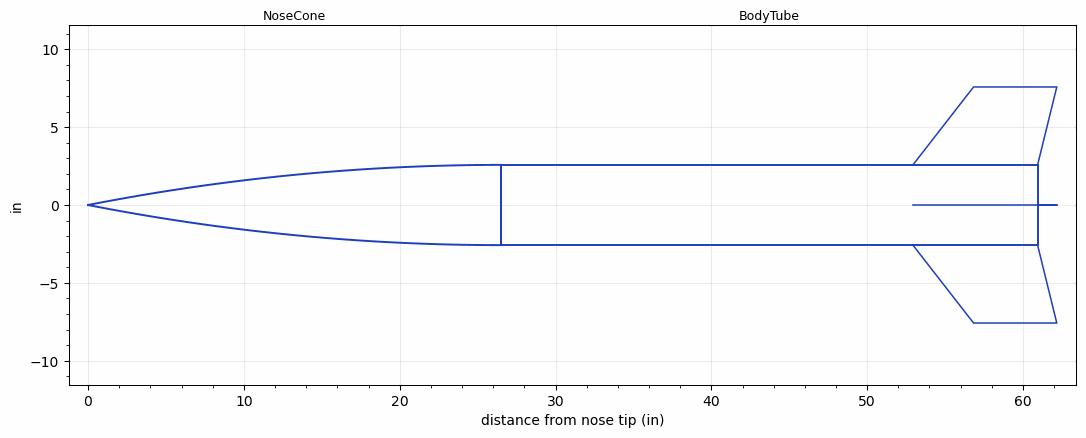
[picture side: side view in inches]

<RASAeroDocument>
 <FileVersion>2</FileVersion>
 <RocketDesign>
  <NoseCone>
   <Length>26.4999</Length>
   <Diameter>5.15</Diameter>
   <Shape>Tangent Ogive</Shape>
   <BluntRadius>0.1</BluntRadius>
   <Location>0</Location>
  </NoseCone>
  <BodyTube>
   <Length>34.438</Length>
   <Diameter>5.15</Diameter>
   <RailGuideDiameter>0.5</RailGuideDiameter>
   <RailGuideHeight>0.187</RailGuideHeight>
   <Location>26.4999</Location>
   <Fin>
    <Count>4</Count>
    <Chord>8</Chord>
    <Span>5</Span>
    <SweepDistance>3.89</SweepDistance>
    <TipChord>5.34</TipChord>
    <Thickness>0.15</Thickness>
    <LERadius>0.05</LERadius>
    <Location>8</Location>
    <AirfoilSection>Square</AirfoilSection>
    <FX1>1</FX1>
    <FX3>0.119</FX3>
   </Fin>
  </BodyTube>
  <Surface>Camouflage Paint</Surface>
  <ModifiedBarrowman>True</ModifiedBarrowman>
  <Turbulence>True</Turbulence>
  <UseBooster1>False</UseBooster1>
  <UseBooster2>False</UseBooster2>
 </RocketDesign>
 <LaunchSite>
  <Altitude>115</Altitude>
  <Pressure>29.92</Pressure>
  <RodAngle>4</RodAngle>
  <RodLength>9</RodLength>
  <Temperature>35</Temperature>
  <WindSpeed>12</WindSpeed>
 </LaunchSite>
 <Recovery>
  <Altitude1>656.168</Altitude1>
  <Altitude2>600</Altitude2>
  <DeviceType1>Parachute</DeviceType1>
  <DeviceType2>Parachute</DeviceType2>
  <Event1>True</Event1>
  <Event2>True</Event2>
  <Size1>24</Size1>
  <Size2>60</Size2>
  <EventType1>Apogee</EventType1>
  <EventType2>Altitude</EventType2>
  <CD1>1.5</CD1>
  <CD2>2.2</CD2>
 </Recovery>
 <SimulationList>
  <Simulation>
   <SustainerEngine>M2050X  (AT)</SustainerEngine>
   <SustainerLaunchWt>24</SustainerLaunchWt>
   <SustainerNozzleDiameter>1.8</SustainerNozzleDiameter>
   <SustainerCG>39.7</SustainerCG>
   <SustainerIgnitionDelay>0</SustainerIgnitionDelay>
   <Booster1SeparationDelay>0</Booster1SeparationDelay>
   <Booster1IgnitionDelay>0</Booster1IgnitionDelay>
   <IncludeBooster1>False</IncludeBooster1>
   <Booster2Delay>0</Booster2Delay>
   <IncludeBooster2>False</IncludeBooster2>
   <TimetoApogee>20.71038</TimetoApogee>
   <MaxAltitude>9658.016</MaxAltitude>
   <MaxVelocity>1391.619</MaxVelocity>
   <OptimumWt>25.08</OptimumWt>
   <OptimumMaxAlt>25.08</OptimumMaxAlt>
  </Simulation>
 </SimulationList>
</RASAeroDocument>
